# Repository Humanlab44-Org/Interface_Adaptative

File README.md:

# Interface_Adaptative
## Contexte et définition du projet 

Nous projetons de construire une interface de jeux pour personnes aux gestes perturbés ou diminués. En effet, pour celles-ci l’utilisation d’un clavier ou d’une manette de jeux classique est difficile voire impossible à utiliser.  
Ce projet a pour but d’élaborer une première interface dévolue aux jeux vidéo et pouvant évoluer vers un objet de domotique 
## Objectif du projet 

Fourniture d’une première interface fonctionnelle de jeux 

Constitution d’un dossier avec : 

- La procédure d’utilisation, 
- La liste du matériel utilisé,  
- Les plans de fabrication, 
- Les schémas de câblage, 
- Le listing du programme 
- Formation des utilisateurs 
- Ouverture d’une discussion avec les utilisateurs pour l’évolution du projet

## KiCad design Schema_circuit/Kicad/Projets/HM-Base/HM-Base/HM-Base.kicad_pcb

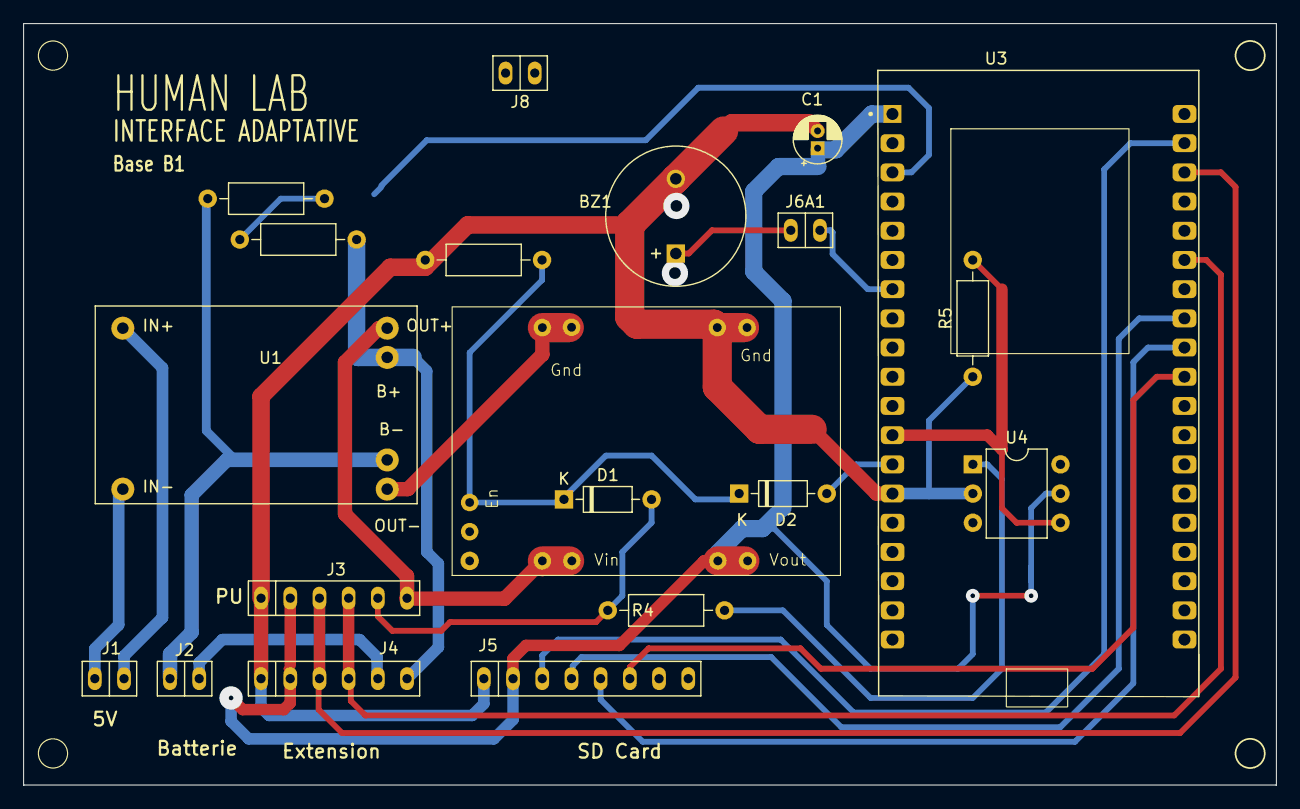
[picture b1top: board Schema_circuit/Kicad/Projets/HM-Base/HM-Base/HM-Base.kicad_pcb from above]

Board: 2 copper layers, 109.0 x 66.2 mm, 20 parts (0 on the bottom side), 24 nets.

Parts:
BZ1: Buzzer; MagneticBuzzer_ProSignal_ABT-410-RC
C1: 10u; CP_Radial_D4.0mm_P1.50mm
D1, D2: 1N4148; D_DO-35_SOD27_P7.62mm_Horizontal
J1, J2, J6A1, J8: Conn_01x02_Socket; SIP-2
J3, J4: Conn_01x06_Socket; SIP-6
J5: Conn_01x08_Socket; SIP-8
R1, R3: 1M; R_Axial_DIN0207_L6.3mm_D2.5mm_P10.16mm_Horizontal
R2: 330k; R_Axial_DIN0207_L6.3mm_D2.5mm_P10.16mm_Horizontal
R4: 560; R_Axial_DIN0207_L6.3mm_D2.5mm_P10.16mm_Horizontal
R5: 33k; R_Axial_DIN0207_L6.3mm_D2.5mm_P10.16mm_Horizontal
U1: TP4056; TP4056-Module
U2: TPS63020; TPS63020DL
U3: ESP32-DEVKITC-32D; MODULE_ESP32-DEVKITC-32D
U4: 4N25; DIP-6_W7.62mm

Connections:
+3.3V: C1.1, J3.2, J4.2, J5.2, U2.5 (Vout1), U3.J2-1 (3V3), U4.5
/CLK: J5.5, U3.J3-9 (IO18)
/CS: J5.6, U3.J3-10 (IO5)
/MISO: J5.4, U3.J3-8 (IO19)
/MOSI: J5.3, U3.J3-2 (IO23)
/SDA: J3.4, J4.4, U3.J3-6 (IO21)
/SLC: J3.3, J4.3, U3.J3-3 (IO22)
GND: BZ1.2 (+), C1.2, J3.1, J4.1, J5.1, J8.1, R3.1, R5.1, U2.7 (Gnd3), U3.J2-14 (GND1), U4.2
unnamed: BZ1.1 (-), J6A1.2
unnamed: D1.2 (A), J3.5, R4.2
unnamed: D1.1 (K), D2.1 (K), R3.2, U2.9 (EN)
unnamed: D2.2 (A), U3.J2-13 (IO12)
unnamed: J1.1, U1.2 (GND1)
unnamed: J1.2, U1.1 (Vin+)
unnamed: J2.1, J4.5
unnamed: J2.2, R1.2, U1.5 (Bat-)
unnamed: J3.6, U1.3 (Vout1), U2.1 (Vin1)
unnamed: J4.6, R2.2, U1.4 (Bat+)
unnamed: J6A1.1, U3.J2-7 (IO32)
unnamed: J8.2, U3.J2-2 (EN)
unnamed: R4.1, U4.1
unnamed: U1.6 (GND2), U2.3 (Gnd1)
unnamed: R5.2, U3.J2-12 (IO14), U4.4
unnamed: R1.1, R2.1, U3.J2-3 (SENSOR_VP)

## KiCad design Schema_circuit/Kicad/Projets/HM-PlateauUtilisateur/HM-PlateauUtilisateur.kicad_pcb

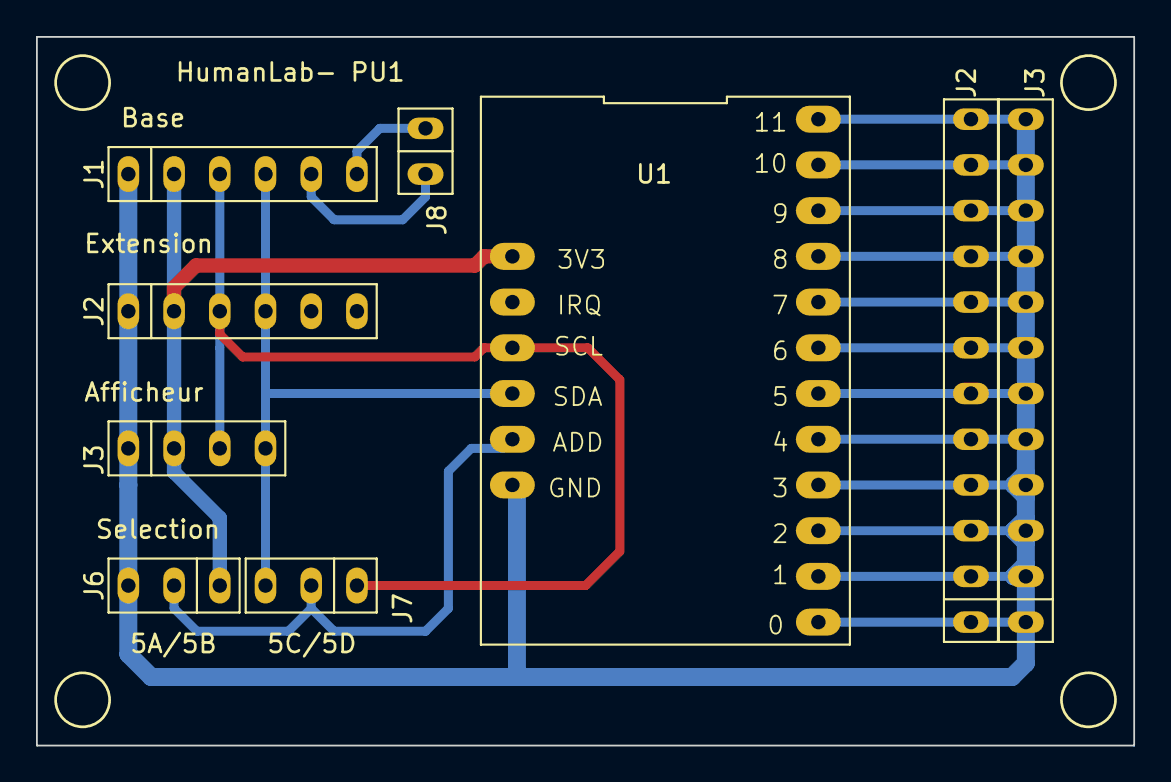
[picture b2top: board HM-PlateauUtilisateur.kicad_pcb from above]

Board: 2 copper layers, 61.0 x 39.4 mm, 9 parts (0 on the bottom side), 19 nets.

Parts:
J1: Vers Base; SIP-6
J2: Exten; SIP-6
J2#2, J3#2: Conn_01x12_Socket; SIP-12
J3: Afficheur; SIP-4
J6: 5A/5B; SIP-3
J7: 5C/5D; SIP-3
J8: Conn_01x02_Socket; SIP-2
U1: MPR121DL; MPR121

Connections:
/3V3: J1.2, J2.2, J3.2, J6.1, U1.1 (3V3)
/GND: J1.1, J2.1, J3.1, J3#2.1, J3#2.2, J3#2.3, J3#2.4, J3#2.5, J3#2.6, J3#2.7, J3#2.8, J3#2.9, J3#2.10, J3#2.11, J3#2.12, J6.3, U1.6 (GND)
/SCL: J1.3, J2.3, J3.3, J7.1, U1.3 (SCL)
/SDA: J1.4, J2.4, J3.4, J7.3, U1.4 (SDA)
unnamed: J1.5, J8.2
unnamed: J1.6, J8.1
unnamed: J2#2.1, U1.7 (ELE0)
unnamed: J2#2.2, U1.8 (ELE1)
unnamed: J2#2.3, U1.9 (ELE2)
unnamed: J2#2.4, U1.10 (ELE3)
unnamed: J2#2.5, U1.11 (LED0/ELE4)
unnamed: J2#2.6, U1.12 (LED1/ELE5)
unnamed: J2#2.7, U1.13 (LED2/ELE6)
unnamed: J2#2.8, U1.14 (LED3/ELE7)
unnamed: J2#2.9, U1.15 (LED4/ELE8)
unnamed: J2#2.10, U1.16 (LED5/ELE9)
unnamed: J2#2.11, U1.17 (LED6/ELE10)
unnamed: J2#2.12, U1.18 (LED7/ELE11)
unnamed: J6.2, J7.2, U1.5 (ADDR)

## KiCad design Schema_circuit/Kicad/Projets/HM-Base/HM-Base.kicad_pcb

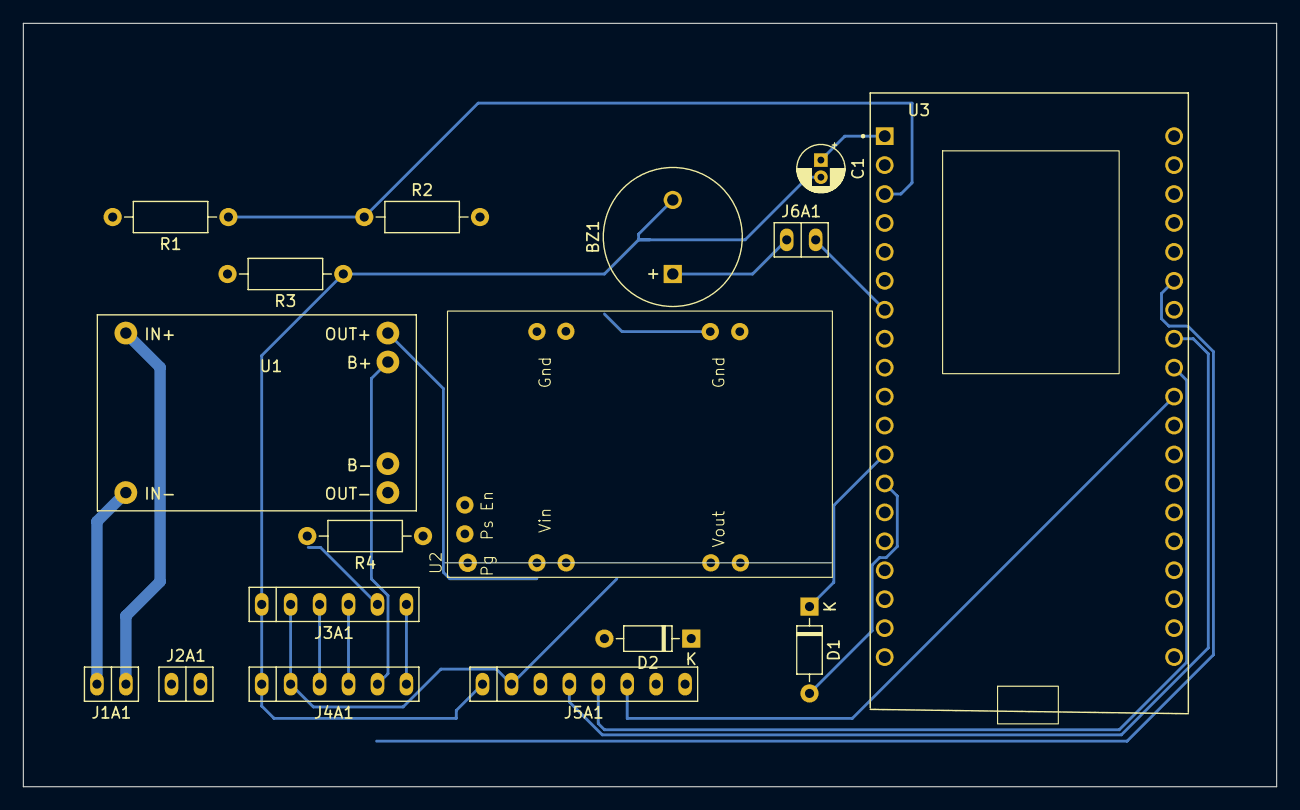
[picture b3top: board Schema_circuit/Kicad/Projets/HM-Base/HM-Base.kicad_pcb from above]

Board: 2 copper layers, 110.0 x 67.0 mm, 17 parts (0 on the bottom side), 22 nets.

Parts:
BZ1: Buzzer; MagneticBuzzer_ProSignal_ABT-410-RC
C1: 10u; CP_Radial_D4.0mm_P1.50mm
D1, D2: 1N4148; D_DO-35_SOD27_P7.62mm_Horizontal
J1A1, J2A1, J6A1: Conn_01x02_Socket; SIP-2
J3A1, J4A1: Conn_01x06_Socket; SIP-6
J5A1: Conn_01x08_Socket; SIP-8
R1: 330K; R_Axial_DIN0207_L6.3mm_D2.5mm_P10.16mm_Horizontal
R2, R3: 1M; R_Axial_DIN0207_L6.3mm_D2.5mm_P10.16mm_Horizontal
R4: 330k; R_Axial_DIN0207_L6.3mm_D2.5mm_P10.16mm_Horizontal
U1: TP4056; TP4056-Module
U2: TPS63020; TPS63020DL
U3: ESP32-DEVKITC-32D; MODULE_ESP32-DEVKITC-32D

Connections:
+3.3V: C1.1, J3A1.2, J4A1.2, J5A1.2, U2.5 (Vout1), U3.J2-1 (3V3)
/CLK: J5A1.5, U3.J3-9 (IO18)
/CS: J5A1.6, U3.J3-10 (IO5)
/MISO: J5A1.4, U3.J3-8 (IO19)
/MOSI: J5A1.3, U3.J3-2 (IO23)
/SDA: J3A1.4, J4A1.4, U3.J3-6 (IO21)
/SLC: J3A1.3, J4A1.3, U3.J3-3 (IO22)
GND: BZ1.2 (+), C1.2, J3A1.1, J4A1.1, J5A1.1, R3.1, U2.7 (Gnd3), U3.J2-14 (GND1)
unnamed: BZ1.1 (-), J6A1.2
unnamed: D1.2 (A), U3.J2-13 (IO12)
unnamed: D1.1 (K), D2.1 (K), R3.2, U2.9 (EN)
unnamed: D2.2 (A), R4.2, U3.J2-12 (IO14)
unnamed: J1A1.1, U1.2 (GND1)
unnamed: J1A1.2, U1.1 (Vin+)
unnamed: J2A1.1, J3A1.6, J4A1.6
unnamed: J2A1.2, R1.2, U1.5 (Bat-)
unnamed: J3A1.5, R4.1
unnamed: J4A1.5, R2.2, U1.4 (Bat+)
unnamed: J6A1.1, U3.J2-7 (IO32)
unnamed: U1.6 (GND2), U2.3 (Gnd1)
unnamed: U1.3 (Vout1), U2.1 (Vin1)
unnamed: R1.1, R2.1, U3.J2-3 (SENSOR_VP)

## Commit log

2023-03-01 ajout du modele de fichier de config
2023-03-04 ajout des codes pour 2 jeux de test
    Les jeux Bejeweled et Burnin Rubber ont été ajouté au fichier abcd.json
    - les codes touches flèches sont à corriger
    - code "barre espace" à ajouter
2023-03-04 Ajout fichier des touches speciales
    la valeur décimale de 'value' est à mettre pour la touche (à terme, le configurateur embarqué fera tout ce travail)
2023-03-04 Mise à jour codes pour les flèches
2023-03-04 Correction erreur de parsing
    Erreur de syntaxe corrigée, manquait des ","
2023-03-12 Creation repertoire Schema_circuit
2023-03-12 Fichier des jeux mis à jour
    Le format a été modifié mais reste compatible avec les anciennes versions..
    le nom de la touche a ete ajouté avec la sensibilité.
    Les ID ont été supprimés...
2023-03-12 Mise à jour
    simplification pour utilisation dans le configurateur
2023-03-12 Mise à jour Schema_circuit
2023-03-13 MàJ2 Schema
2023-03-14 ajout schéma
2023-03-15 MàJ3 dossier Schema_circuit
2023-03-23 Schemas sous Kicad
2023-03-24 Rectification schema BASE
2023-03-24 Rectification fichier Base.pdf
2023-03-24 Rangement Dossier Proteus
2023-03-29 MaJ 29-04-23
2023-03-30 Circuits archivés
2023-03-31 correctif sur PCB PU1
2023-04-02 MaJ PCB Base v4
2023-04-03 Support afficheur ds Montage3D
2023-04-21 MaJ Base
2023-04-21 MaJ Afficheur
2023-04-25 Maj2 Base
2023-04-27 Nettoyage et MàJ dossier Schema_circuit
2023-04-27 Nettoyage et MàJ Afficheur
2023-05-24 MàJ schema et PCB
2024-06-20 Création du sous répertoire programme
2024-06-20 Add program files
2024-06-20 add SDcard files
2024-06-20 add some lif files
2025-04-19 Create documentation_a_mettre _ici
